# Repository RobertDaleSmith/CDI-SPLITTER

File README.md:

# CDI Controller Splitter

A simple controller splitter for CD-i consoles with only a single controller port. This repository includes KiCad PCB files and 3D printable shell files.

Originally sold by: [controlleradapter.com/products/cd-i-splitter](https://controlleradapter.com/products/cd-i-splitter)

Also available on Flux.ai: [flux.ai/robertdalesmith/cd-i-controller-splitter](https://www.flux.ai/robertdalesmith/cd-i-controller-splitter)

3D files also can be found on Printables: [printables.com/model/337269-cd-i-splitter-shell](https://www.printables.com/model/337269-cd-i-splitter-shell)

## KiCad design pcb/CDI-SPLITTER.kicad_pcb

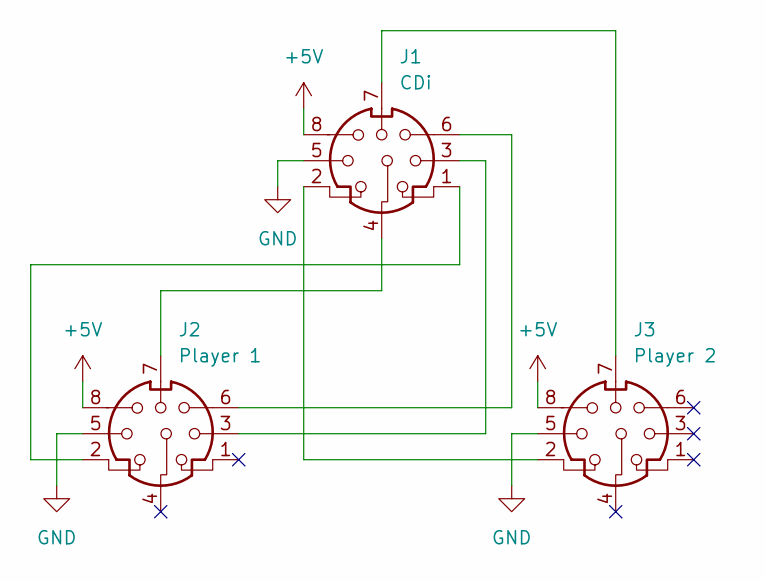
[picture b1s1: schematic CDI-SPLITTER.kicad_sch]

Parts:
J1: CDi; 57492671
J2: Player 1; 57492671
J3: Player 2; 57492671

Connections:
+5V: J1.8, J2.8, J3.8
GND: J1.5, J1.MH1, J1.MH2, J1.MH3, J2.5, J2.MH1, J2.MH2, J2.MH3, J3.5, J3.MH1, J3.MH2, J3.MH3
unnamed: J1.1, J2.2
unnamed: J1.2, J3.2
unnamed: J1.3, J2.3
unnamed: J1.4, J2.7
unnamed: J1.6, J2.6
unnamed: J1.7, J3.7

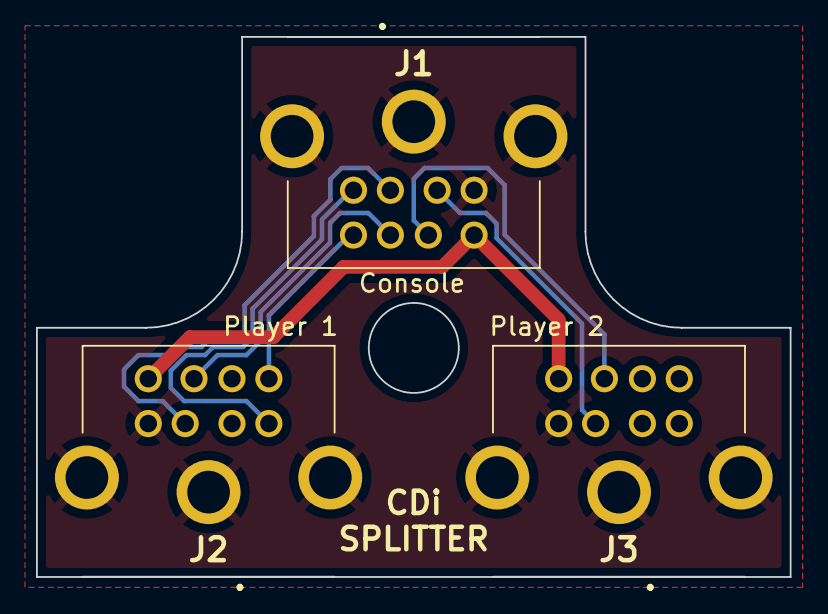
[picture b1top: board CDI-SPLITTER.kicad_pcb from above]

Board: 2 copper layers, 41.9 x 30.0 mm, 3 parts (0 on the bottom side), 8 nets.

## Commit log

2022-02-10 feature(pcb): creates cdi controller splitter v01 pcb
2024-02-14 feature(case): adds case/shell 3d model files
2024-02-14 chore: updates readme with links to external sources
